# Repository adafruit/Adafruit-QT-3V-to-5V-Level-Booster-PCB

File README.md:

## Adafruit QT 3V to 5V Level Booster Breakout - STEMMA QT / Qwiic PCB

<a href="http://www.adafruit.com/products/5649"><br/>
Click here to purchase one from the Adafruit shop</a>

PCB files for the Adafruit QT 3V to 5V Level Booster Breakout - STEMMA QT. 

Format is EagleCAD schematic and board layout
* https://www.adafruit.com/product/5649

### Description

If you're looking to use the Qwiic / Stemma QT standard for your next project - but you're using a sensor or device that requires 5V power or logic, this board is designed for you! It will let you use the 3V power and logic from your Raspberry Pi, or ARM Cortex microcontroller, and boost/shift it up to 5V for use with older or high-power devices that aren't happy with only 3V.

These days, almost every microcontroller / microcomputer board has 3V power and logic: ESP32 series, ATSAMD chips, RP2040 boards, micro:bits, etc! But we still see sensors and devices here and there that really want 5V power or logic. Like this Sensirion SEN54 which has a small motor with 5V power requirements.

On one side of this board is 3V power and logic level inputs. In the middle is a 5V charge-pump boosting regulator that can provide 100mA continuous (250mA peak) plus level shifting circuitry. On the opposite side is the same I2C traffic but now safely shifted up to 5V. If you happen to be using a board that wants 5V power, but 3V logic I2C, there's a solder jumper on the back you can cut/solder to set the output logic level to unshifted 3V.

It's simple but very effective! You also get breadboard breakout pins for breadboard usage so it can also be used as a QT-to-perfboard adapter. If you need something that does 5V to 3V down-conversion, we have that in the shop as well.

The STEMMA QT connectors on either side are compatible with the  I2C connectors. This allows you to make solderless connections between your development board and the QT Shifter or to chain it with a wide range of other sensors and accessories using a compatible cable. QT Cable is not included, but we have a variety in the shop. 

### License

Adafruit invests time and resources providing this open source design, please support Adafruit and open-source hardware by purchasing products from [Adafruit](https://www.adafruit.com)!

Designed by Limor Fried/Ladyada for Adafruit Industries.

Creative Commons Attribution/Share-Alike, all text above must be included in any redistribution. 
See license.txt for additional details.

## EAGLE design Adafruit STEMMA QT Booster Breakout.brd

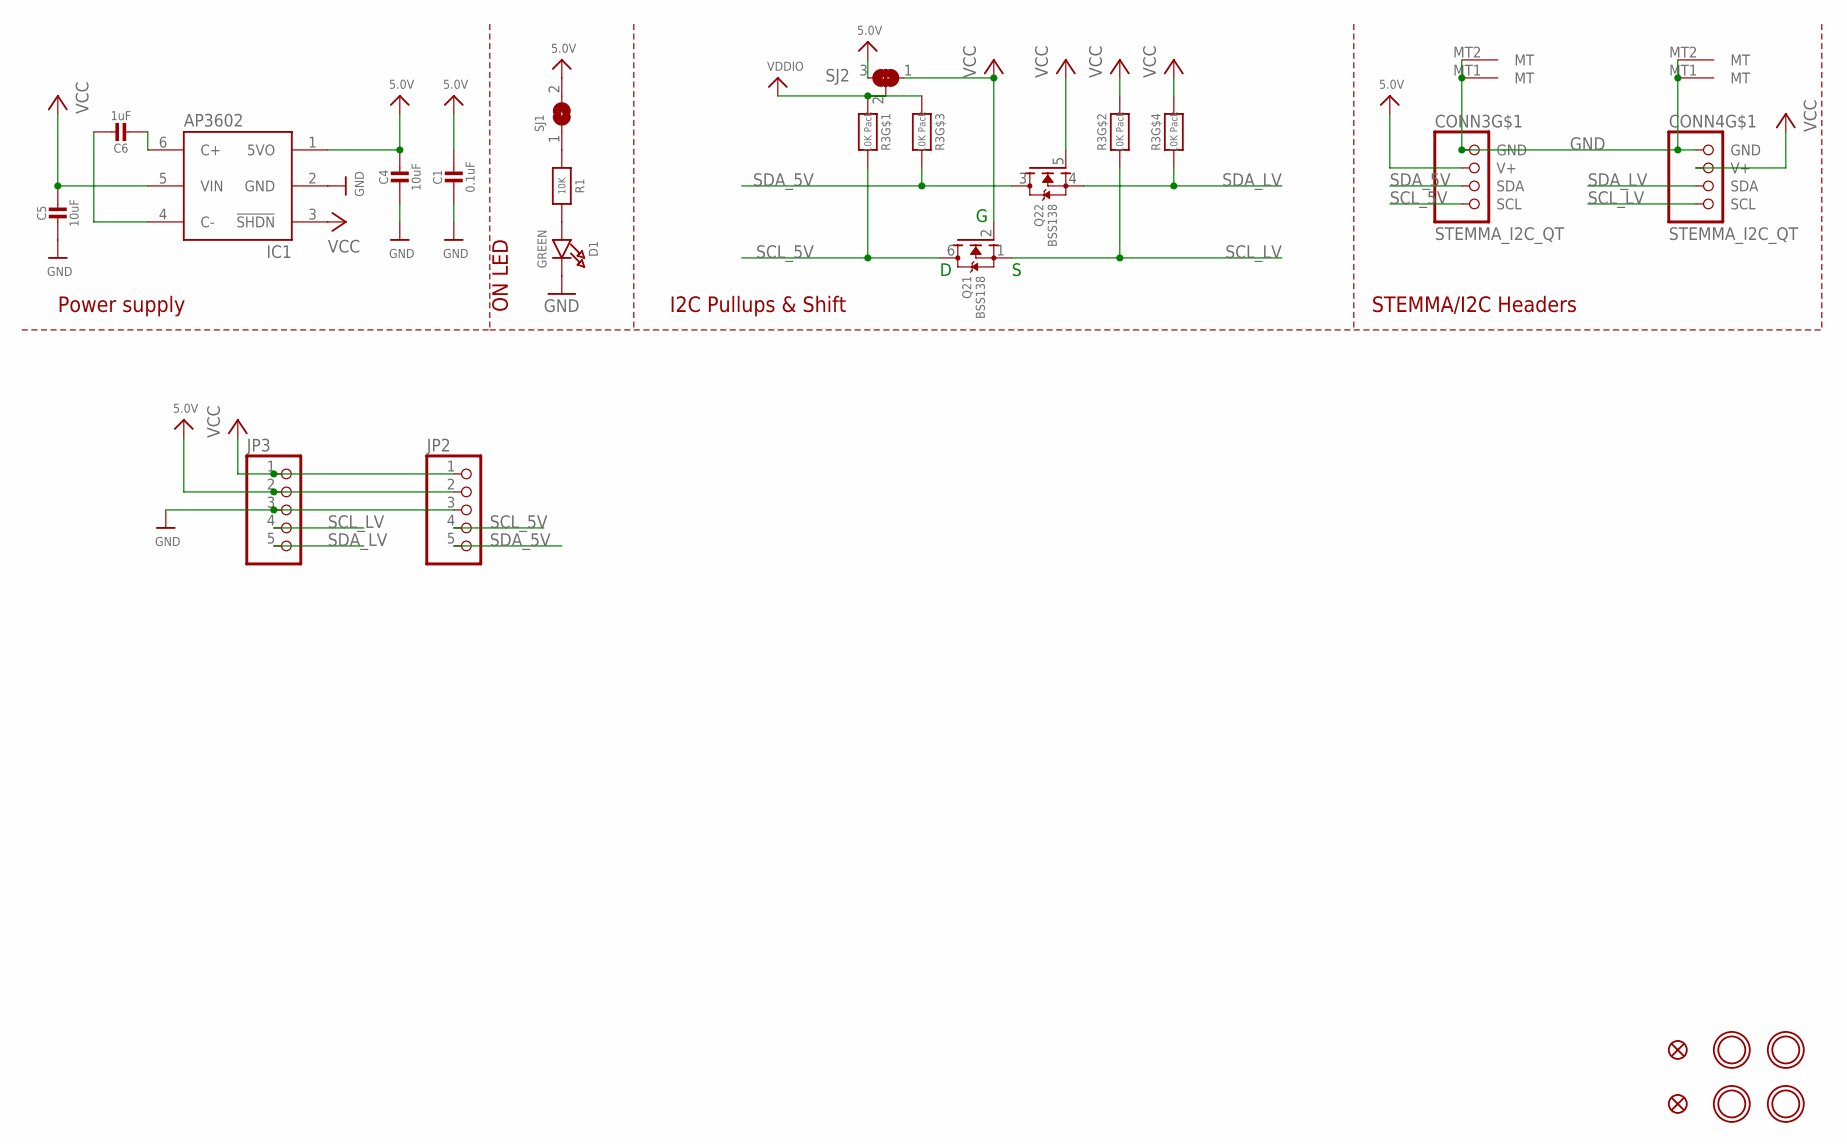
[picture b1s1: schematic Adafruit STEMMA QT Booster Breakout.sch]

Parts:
C1: 0.1uF; 0603-NO
C4, C5: 10uF; 0805-NO
C6: 1uF; 0805-NO
CONN3, CONN4: STEMMA_I2C_QT; JST_SH4
D1: GREEN; CHIPLED_0603_NOOUTLINE
FID3, FID4: FIDUCIAL_1MM
IC1: AP3602/RT9361; SOT23-6
JP2, JP3: HEADER-1X576MIL; 1X05_ROUND_76
Q2: BSS138; SOT363
R1: 10K; 0603-NO
R3: 10K Pack; RESPACK_4X0603
SJ1: SOLDERJUMPERCLOSED; SOLDERJUMPER_CLOSEDWIRE
SJ2: SOLDERJUMPER_2WAY; SOLDERJUMPER_2WAY_OPEN_NOPASTE
U$1, U$17, U$19, U$21: MOUNTINGHOLE2.5; MOUNTINGHOLE_2.5_PLATED

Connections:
5.0V: C1.1, C4.1, CONN3.2 (V+), IC1.1 (5VO), JP2.2, JP3.2, SJ1.2, SJ2.3
GND: C1.2, C4.2, C5.2, CONN3.1 (GND), CONN3.MT1 (MT), CONN3.MT2 (MT), CONN4.1 (GND), CONN4.MT1 (MT), CONN4.MT2 (MT), D1.C, IC1.2 (GND), JP2.3, JP3.3
unnamed: D1.A, R1.2
unnamed: R1.1, SJ1.1
unnamed: C6.2, IC1.6 (C+)
unnamed: C6.1, IC1.4 (C-)
SCL_5V: CONN3.4 (SCL), JP2.4, Q2.6 (D), R3.8 (2)
SCL_LV: CONN4.4 (SCL), JP3.4, Q2.1 (S), R3.7 (2)
SDA_5V: CONN3.3 (SDA), JP2.5, Q2.3 (D), R3.6 (2)
SDA_LV: CONN4.3 (SDA), JP3.5, Q2.4 (S), R3.5 (2)
VCC: C5.1, CONN4.2 (V+), IC1.3 (!SHDN), IC1.5 (VIN), JP2.1, JP3.1, Q2.2 (G), Q2.5 (G), R3.2 (1), R3.4 (1), SJ2.1
VDDIO: R3.1, R3.3 (1), SJ2.2

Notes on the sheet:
I2C Pullups & Shift
STEMMA/I2C Headers
ON LED
Power supply

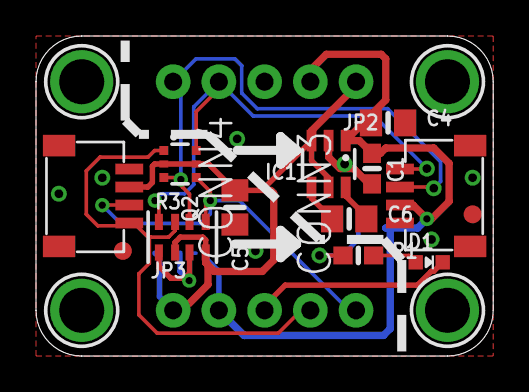
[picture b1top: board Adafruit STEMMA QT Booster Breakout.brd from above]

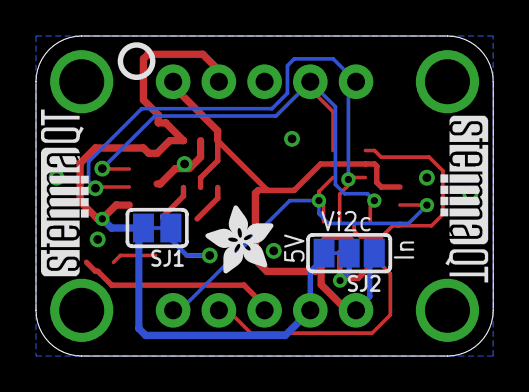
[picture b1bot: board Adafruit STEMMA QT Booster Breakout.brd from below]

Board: 2 copper layers, 25.4 x 17.8 mm, 40 parts (8 on the bottom side), 12 nets.

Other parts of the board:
PLABEL0: PLABEL0
PLABEL1: PLABEL1
PLABEL2: PLABEL2
PLABEL3: PLABEL3
PLABEL4: PLABEL4
PLABEL5: PLABEL5
PLABEL6: PLABEL6
PLABEL7: PLABEL7
PLABEL8: PLABEL8
PLABEL9: PLABEL9
PLABEL10: PLABEL10
PLABEL11: PLABEL11
PLABEL12: PLABEL12
PLABEL13: PLABEL13
PLABEL14: PLABEL14
U$2: ADAFRUIT_3.5MM
U$25: PCBFEAT-REV-040
U$30, U$31: STEMMAQT

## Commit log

2022-12-22 cookiecutter output
2022-12-22 adding copy

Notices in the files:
parts and their libraries:
microbuilder: This work is placed in the public domain, and may be freely used for commercial and non-commercial work with the following conditions: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
